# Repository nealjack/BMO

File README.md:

BMO
===

Code, Art and Design files to make BMO from adventure time

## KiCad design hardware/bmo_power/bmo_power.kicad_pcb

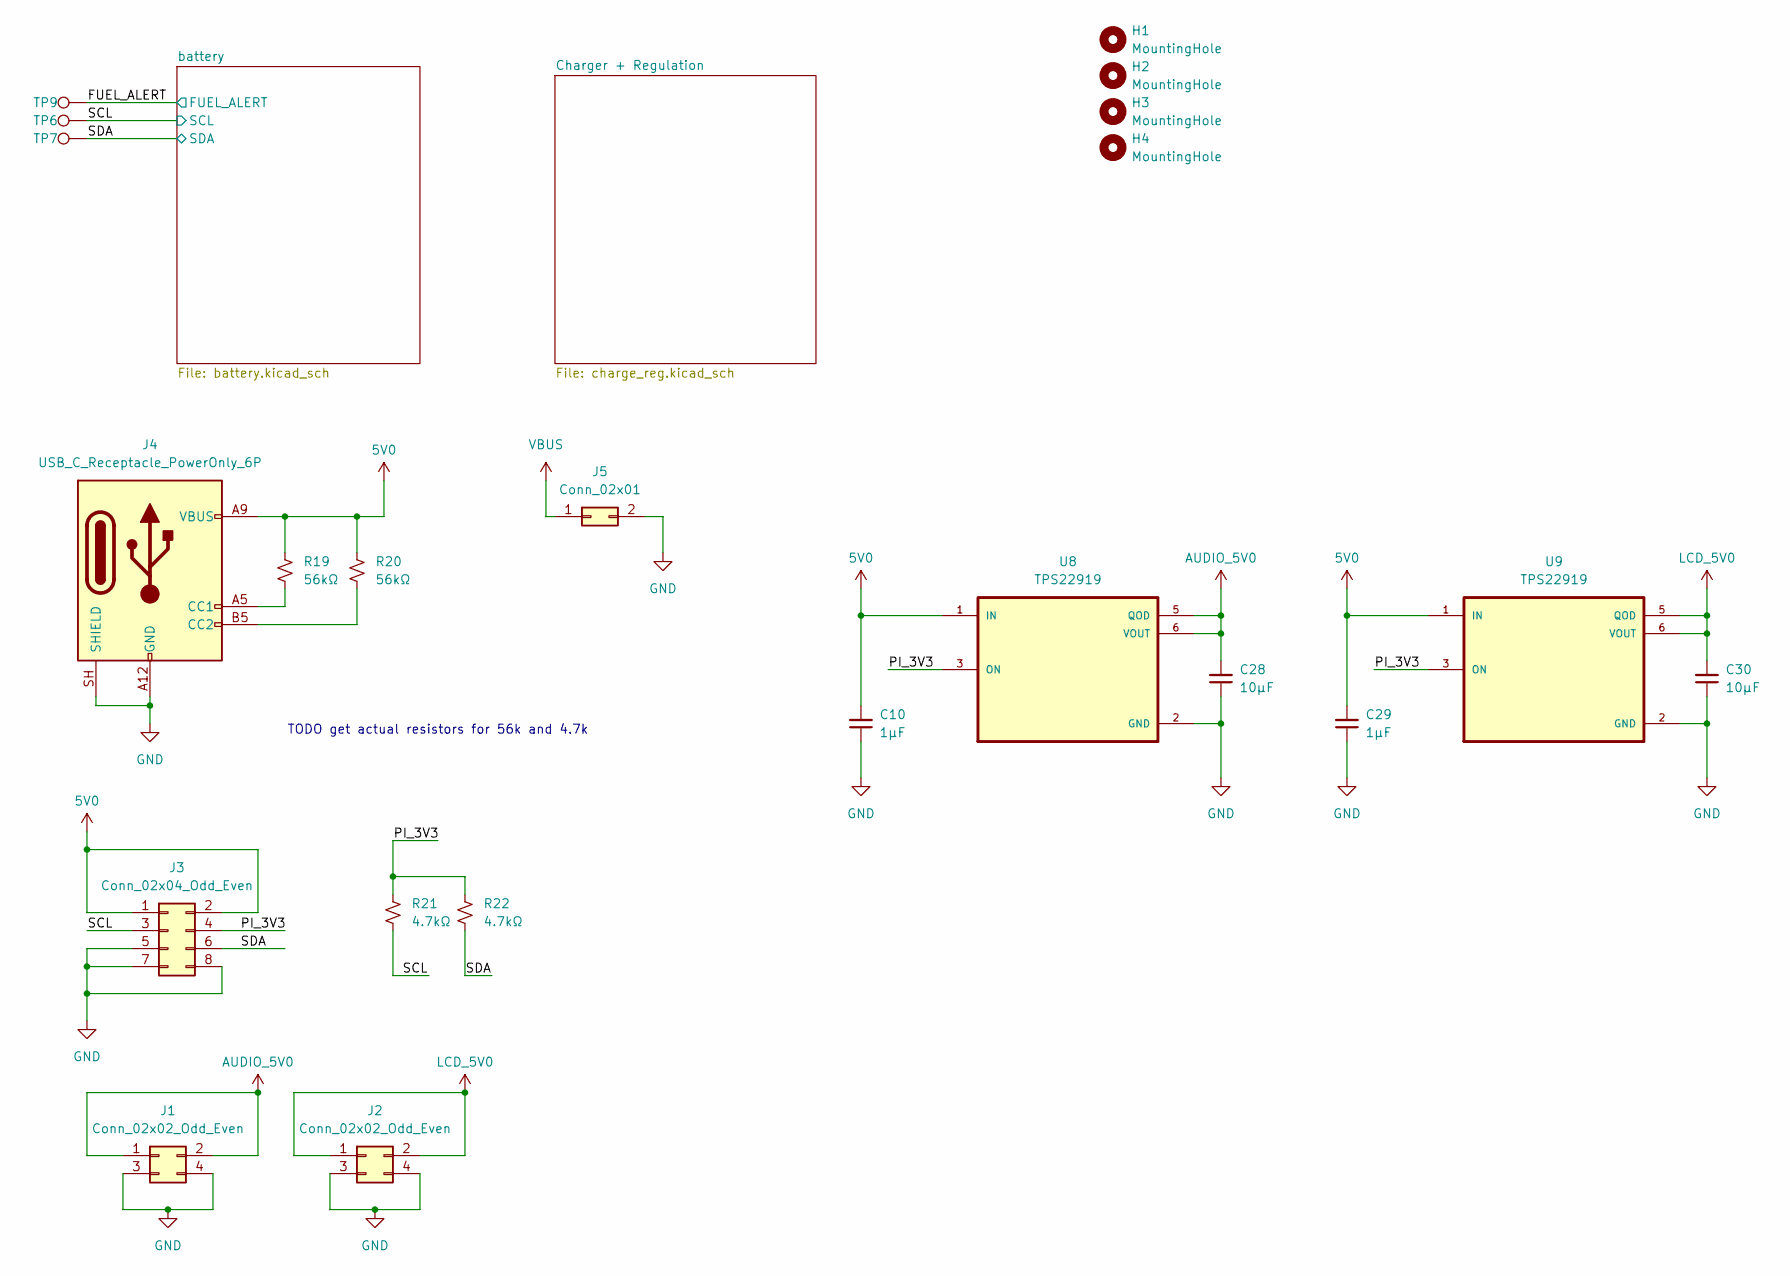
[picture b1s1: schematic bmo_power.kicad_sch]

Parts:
C10, C29: 1µF; C_0402_1005Metric_Pad0.74x0.62mm_HandSolder; MPN CL05A105KP5NNNC; Digikey 1276-1076-1-ND
C28, C30: 10µF; C_0402_1005Metric_Pad0.74x0.62mm_HandSolder; MPN GRM155R61A106ME11D; Digikey GRM155R61A106ME11D
H1, H2, H3, H4: MountingHole; MountingHole_2.7mm_M2.5
J1, J2: Conn_02x02_Odd_Even; PinHeader_2x02_P2.54mm_Vertical
J3: Conn_02x04_Odd_Even; PinHeader_2x04_P2.54mm_Vertical
J4: USB_C_Receptacle_PowerOnly_6P; USB_C_Receptacle_GCT_USB4125-xx-x-0190_6P_TopMnt_Horizontal
J5: Conn_02x01; PinSocket_2x01_P2.54mm_Vertical
R19, R20: 56kΩ; R_0402_1005Metric_Pad0.72x0.64mm_HandSolder; MPN RMCF0402FT10K0; Digikey RMCF0402FT10K0CT-ND
R21, R22: 4.7kΩ; R_0402_1005Metric_Pad0.72x0.64mm_HandSolder; MPN RMCF0402FT10K0; Digikey RMCF0402FT10K0CT-ND
TP6, TP7, TP9: TestPoint; TestPoint_Pad_2.0x2.0mm
U8, U9: TPS22919; SOT-363_SC-70-6

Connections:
5V0: C10.2, C29.2, J3.1, J3.2, J4.A9 (VBUS), J4.B9 (VBUS), R19.1, R20.1, U8.1 (IN), U9.1 (IN); also elsewhere on the board
/FUEL_ALERT: TP9.1 (1_1); also elsewhere on the board
/PI_3V3: J3.4, R21.1, R22.1, U8.3 (ON), U9.3 (ON)
/SCL: J3.3, R21.2, TP6.1 (1_1); also elsewhere on the board
/SDA: J3.6, R22.2, TP7.1 (1_1); also elsewhere on the board
AUDIO_5V0: C28.2, J1.1, J1.2, U8.5 (QOD), U8.6 (VOUT)
GND: C10.1, C28.1, C29.1, C30.1, J1.3, J1.4, J2.3, J2.4, J3.5, J3.7, J3.8, J4.A12 (GND), J4.B12 (GND), J4.SH (SHIELD), J5.2, U8.2 (GND), U9.2 (GND); also elsewhere on the board
LCD_5V0: C30.2, J2.1, J2.2, U9.5 (QOD), U9.6 (VOUT)
unnamed: J4.A5 (CC1), R19.2
unnamed: J4.B5 (CC2), R20.2
VBUS: J5.1; also elsewhere on the board

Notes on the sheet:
TODO get actual resistors for 56k and 4.7k

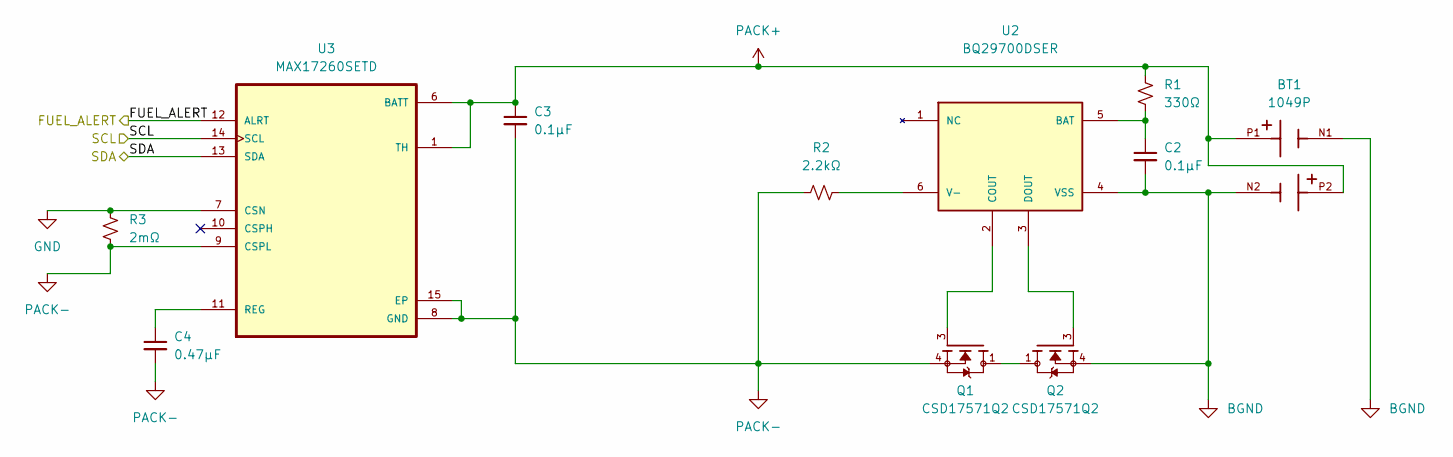
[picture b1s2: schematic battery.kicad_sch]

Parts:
BT1: 1049P; BAT_1049P; PARTREV F
C2, C3: 0.1μF; C_0402_1005Metric_Pad0.74x0.62mm_HandSolder; Tolerance 10%; Voltage 10V; MPN GRM155R61A104KA01D; Digikey 490-1318-2-ND
C4: 0.47μF; C_0402_1005Metric_Pad0.74x0.62mm_HandSolder; Tolerance 10%; Voltage 6.3V; MPN GRM155R60J474KE19D; Digikey 490-3266-1-ND
Q1, Q2: CSD17571Q2; TRANS_CSD17571Q2; PARTREV A
R1: 330Ω; R_0402_1005Metric_Pad0.72x0.64mm_HandSolder; MPN RMCF0402JT330R; Digikey RMCF0402JT330RCT-ND
R2: 2.2kΩ; R_0402_1005Metric_Pad0.72x0.64mm_HandSolder; Tolerance 5%; MPN RMCF0402JT2K20; Digikey RMCF0402JT2K20TR-ND
R3: 2mΩ; R_2512_6332Metric; Tolerance 1%; MPN CSNL2512FT2L00; Digikey CSNL2512FT2L00CT-ND
U2: BQ29700DSER; SON50P150X150X80-6N; PARTREV G
U3: MAX17260SETD; SON40P300X300X80-15N

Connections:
/FUEL_ALERT: U3.12 (ALRT); also elsewhere on the board
/SCL: U3.14 (SCL); also elsewhere on the board
/SDA: U3.13 (SDA); also elsewhere on the board
BGND: BT1.N1, BT1.N2, C2.2, Q2.4, Q2.8, U2.4 (VSS)
GND: R3.1, U3.7 (CSN); also elsewhere on the board
unnamed: Q1.1, Q1.2, Q1.5, Q1.6, Q1.7, Q2.1, Q2.2, Q2.5, Q2.6, Q2.7
unnamed: C2.1, R1.1, U2.5 (BAT)
unnamed: Q1.3, U2.2 (COUT)
unnamed: Q2.3, U2.3 (DOUT)
unnamed: R2.2, U2.6 (V-)
unnamed: C4.1, U3.11 (REG)
PACK+: BT1.P1, BT1.P2, C3.1, R1.2, U3.1 (TH), U3.6 (BATT); also elsewhere on the board
PACK-: C3.2, C4.2, Q1.4, Q1.8, R2.1, R3.2, U3.8 (GND), U3.9 (CSPL), U3.15 (EP)

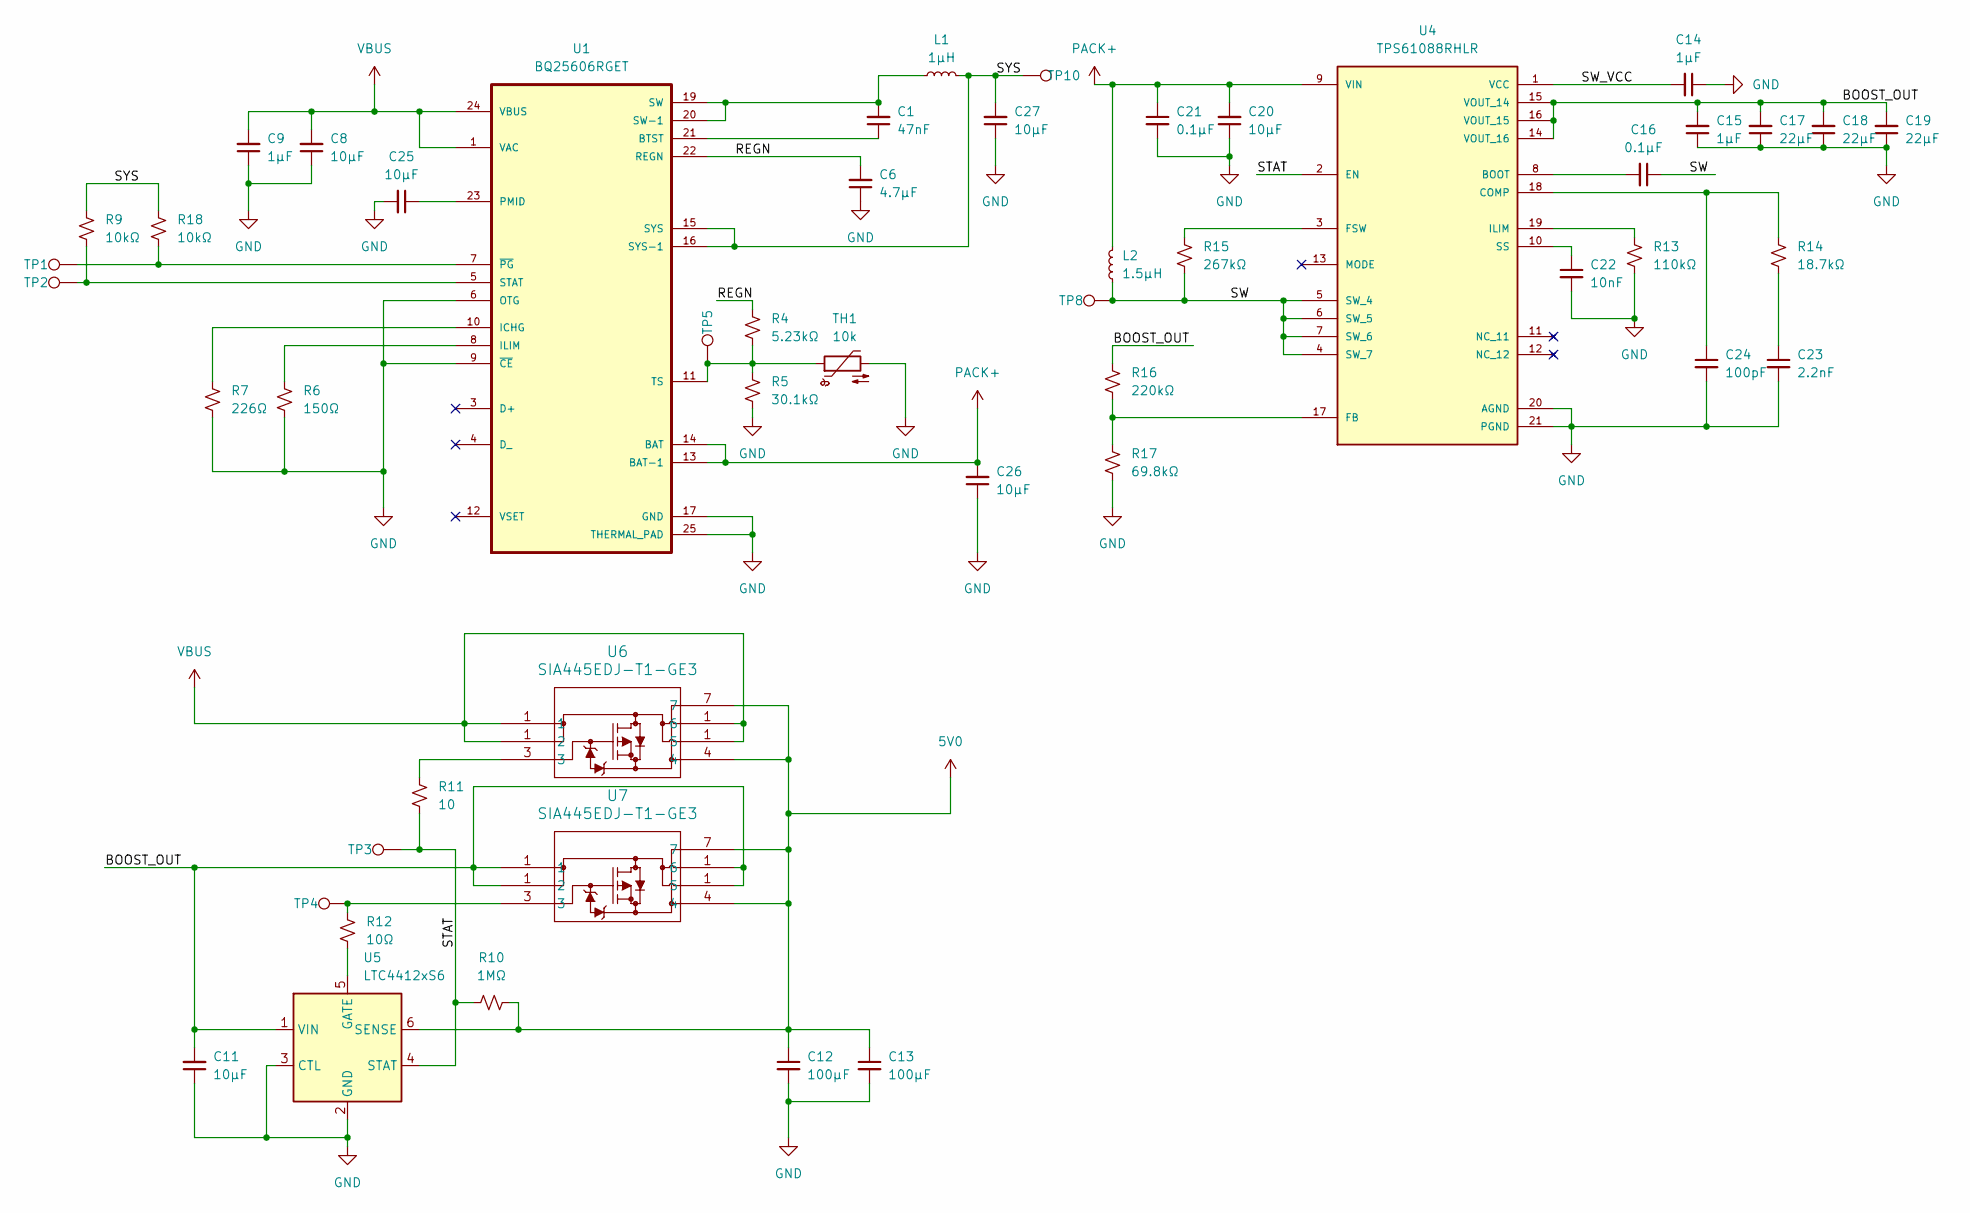
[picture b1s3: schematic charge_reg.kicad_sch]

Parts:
C1: 47nF; C_0402_1005Metric_Pad0.74x0.62mm_HandSolder; MPN GRM155R61A473KA01D; Digikey 490-5412-1-ND
C6: 4.7µF; C_0402_1005Metric_Pad0.74x0.62mm_HandSolder; MPN CL05A475MP5NRNC; Digikey 1276-1482-1-ND
C8, C11, C20, C25, C26, C27: 10µF; C_0402_1005Metric_Pad0.74x0.62mm_HandSolder; MPN GRM155R61A106ME11D; Digikey GRM155R61A106ME11D
C9, C14, C15: 1µF; C_0402_1005Metric_Pad0.74x0.62mm_HandSolder; MPN CL05A105KP5NNNC; Digikey 1276-1076-1-ND
C12, C13: 100µF; C_1206_3216Metric; MPN GRM31CR61A107MEA8L; Digikey 490-GRM31CR61A107MEA8LCT-ND
C16, C21: 0.1μF; C_0402_1005Metric_Pad0.74x0.62mm_HandSolder; Tolerance 10%; Voltage 10V; MPN GRM155R61A104KA01D; Digikey 490-1318-2-ND
C17, C18, C19: 22µF; C_0603_1608Metric; MPN CL10A226MP8NUNE; Digikey 1276-1274-1-ND
C22: 10nF; C_0402_1005Metric_Pad0.74x0.62mm_HandSolder; Tolerance 10%; Voltage 10V; MPN GRM155R61A103KA01D; Digikey 490-6296-1-ND
C23: 2.2nF; C_0402_1005Metric_Pad0.74x0.62mm_HandSolder; Tolerance 10%; Voltage 10V; MPN CC0402KRX7R6BB222; Digikey 311-3792-1-ND
C24: 100pF; C_0402_1005Metric_Pad0.74x0.62mm_HandSolder; Tolerance 10%; Voltage 10V; MPN CC0402KRX7R6BB101; Digikey 13-CC0402KRX7R6BB101CT-ND
L1: 1μH; L_Vishay_IHLP-2020; MPN IHLP2020ABER1R0M01; Digikey 541-1704-1-ND
L2: 1.5µH; 74439324015; MPN 74439324015; Digikey 732-74439324015CT-ND
R4: 5.23kΩ; R_0402_1005Metric_Pad0.72x0.64mm_HandSolder; MPN RC0402FR-075K23L; Digikey YAG3195CT-ND
R5: 30.1kΩ; R_0402_1005Metric_Pad0.72x0.64mm_HandSolder; MPN RC0402FR-0730K1L; Digikey 311-30.1KLRCT-ND
R6: 150Ω; R_0402_1005Metric_Pad0.72x0.64mm_HandSolder; MPN ERJ-2RKF1500X; Digikey P150LCT-ND
R7: 226Ω; R_0402_1005Metric_Pad0.72x0.64mm_HandSolder; MPN RMCF0402FT226R; Digikey RMCF0402FT226RCT-ND
R9, R18: 10kΩ; R_0402_1005Metric_Pad0.72x0.64mm_HandSolder; MPN RMCF0402FT10K0; Digikey RMCF0402FT10K0CT-ND
R10: 1MΩ; R_0402_1005Metric_Pad0.72x0.64mm_HandSolder; MPN RC0402FR-071ML; Digikey 311-1.00MLRCT-ND
R11: 10; R_0402_1005Metric_Pad0.72x0.64mm_HandSolder; MPN RC0402FR-0710RL; Digikey 311-10.0LRCT-ND
R12: 10Ω; R_0402_1005Metric_Pad0.72x0.64mm_HandSolder; MPN RC0402FR-0710RL; Digikey 311-10.0LRCT-ND
R13: 110kΩ; R_0402_1005Metric_Pad0.72x0.64mm_HandSolder; MPN RC0402FR-07110KL; Digikey 311-110KLRCT-ND
R14: 18.7kΩ; R_0402_1005Metric_Pad0.72x0.64mm_HandSolder; MPN RMCF0402FT18K7; Digikey RMCF0402FT18K7CT-ND
R15: 267kΩ; R_0402_1005Metric_Pad0.72x0.64mm_HandSolder; MPN RMCF0402FT267K; Digikey RMCF0402FT267KCT-ND
R16: 220kΩ; R_0402_1005Metric_Pad0.72x0.64mm_HandSolder; MPN RC0402FR-07220KL; Digikey 311-220KLRCT-ND
R17: 69.8kΩ; R_0402_1005Metric_Pad0.72x0.64mm_HandSolder; MPN RMCF0402FT69K8; Digikey RMCF0402FT69K8CT-ND
TH1: 10k; PinHeader_1x02_P2.54mm_Vertical; MPN 103AT-2; Digikey 4316-103AT-2-ND
TP1, TP2, TP3, TP4, TP5, TP8, TP10: TestPoint; TestPoint_Pad_2.0x2.0mm
U1: BQ25606RGET; QFN50P400X400X100-25N
U4: TPS61088RHLR; IC_TPS61088RHLR; PARTREV 4219071/A 05/2017
U5: LTC4412xS6; TSOT-23-6
U6, U7: SIA445EDJ-T1-GE3; Vishay_PowerPAK_SC70-6L_Single

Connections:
5V0: C12.1, C13.1, R10.2, U5.6 (SENSE), U6.4, U6.7, U7.4, U7.7; also elsewhere on the board
/Charger + Regulation/BOOST_OUT: C11.2, C15.2, C17.2, C18.2, C19.2, R16.1, U4.14 (VOUT_16), U4.15 (VOUT_14), U4.16 (VOUT_15), U5.1 (VIN), U7.1
/Charger + Regulation/REGN: C6.2, R4.1, U1.22 (REGN)
/Charger + Regulation/STAT: R10.1, R11.2, TP3.1 (1_1), U4.2 (EN), U5.4 (STAT)
/Charger + Regulation/SW: C16.1, L2.1, R15.2, TP8.1 (1_1), U4.4 (SW_7), U4.5 (SW_4), U4.6 (SW_5), U4.7 (SW_6)
/Charger + Regulation/SW_VCC: C14.2, U4.1 (VCC)
/Charger + Regulation/SYS: C27.2, L1.2, R9.1, R18.1, TP10.1 (1_1), U1.15 (SYS), U1.16 (SYS-1)
GND: C6.1, C8.1, C9.1, C11.1, C12.2, C13.2, C14.1, C15.1, C17.1, C18.1, C19.1, C20.1, C21.2, C22.2, C23.2, C24.2, C25.2, C26.1, C27.1, R5.2, R6.1, R7.1, R13.1, R17.2, TH1.2, U1.6 (OTG), U1.9 (~CE), U1.17 (GND), U1.18 (GND), U1.25 (THERMAL_PAD), U4.20 (AGND), U4.21 (PGND), U4.22 (PGND), U4.23 (PGND), U4.24 (PGND), U4.25 (PGND), U4.26 (PGND), U4.27 (PGND), U4.28 (PGND), U4.29 (PGND), U5.2 (GND), U5.3 (CTL); also elsewhere on the board
unnamed: C23.1, R14.1
unnamed: R11.1, U6.3
unnamed: R12.1, TP4.1 (1_1), U7.3
unnamed: C1.1, U1.21 (BTST)
unnamed: R7.2, U1.10 (ICHG)
unnamed: R6.2, U1.8 (ILIM)
unnamed: C25.1, U1.23 (PMID)
unnamed: R9.2, TP2.1 (1_1), U1.5 (STAT)
unnamed: C1.2, L1.1, U1.19 (SW), U1.20 (SW-1)
unnamed: R4.2, R5.1, TH1.1, TP5.1 (1_1), U1.11 (TS)
unnamed: R18.2, TP1.1 (1_1), U1.7 (~PG)
unnamed: C16.2, U4.8 (BOOT)
unnamed: C24.1, R14.2, U4.18 (COMP)
unnamed: R16.2, R17.1, U4.17 (FB)
unnamed: R15.1, U4.3 (FSW)
unnamed: R13.2, U4.19 (ILIM)
unnamed: C22.1, U4.10 (SS)
unnamed: R12.2, U5.5 (GATE)
PACK+: C20.2, C21.1, C26.2, L2.2, U1.13 (BAT-1), U1.14 (BAT), U4.9 (VIN); also elsewhere on the board
VBUS: C8.2, C9.2, U1.1 (VAC), U1.24 (VBUS), U6.1; also elsewhere on the board

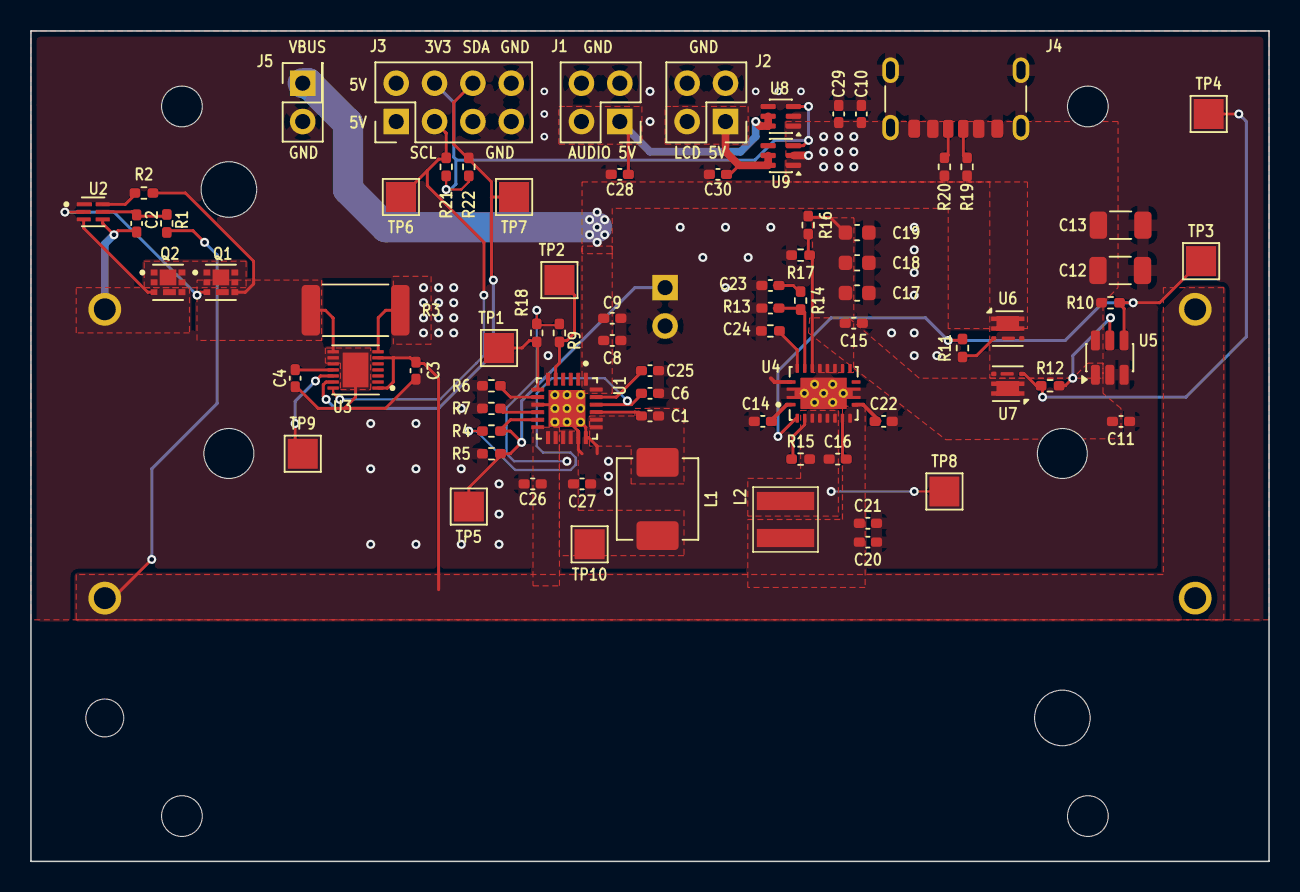
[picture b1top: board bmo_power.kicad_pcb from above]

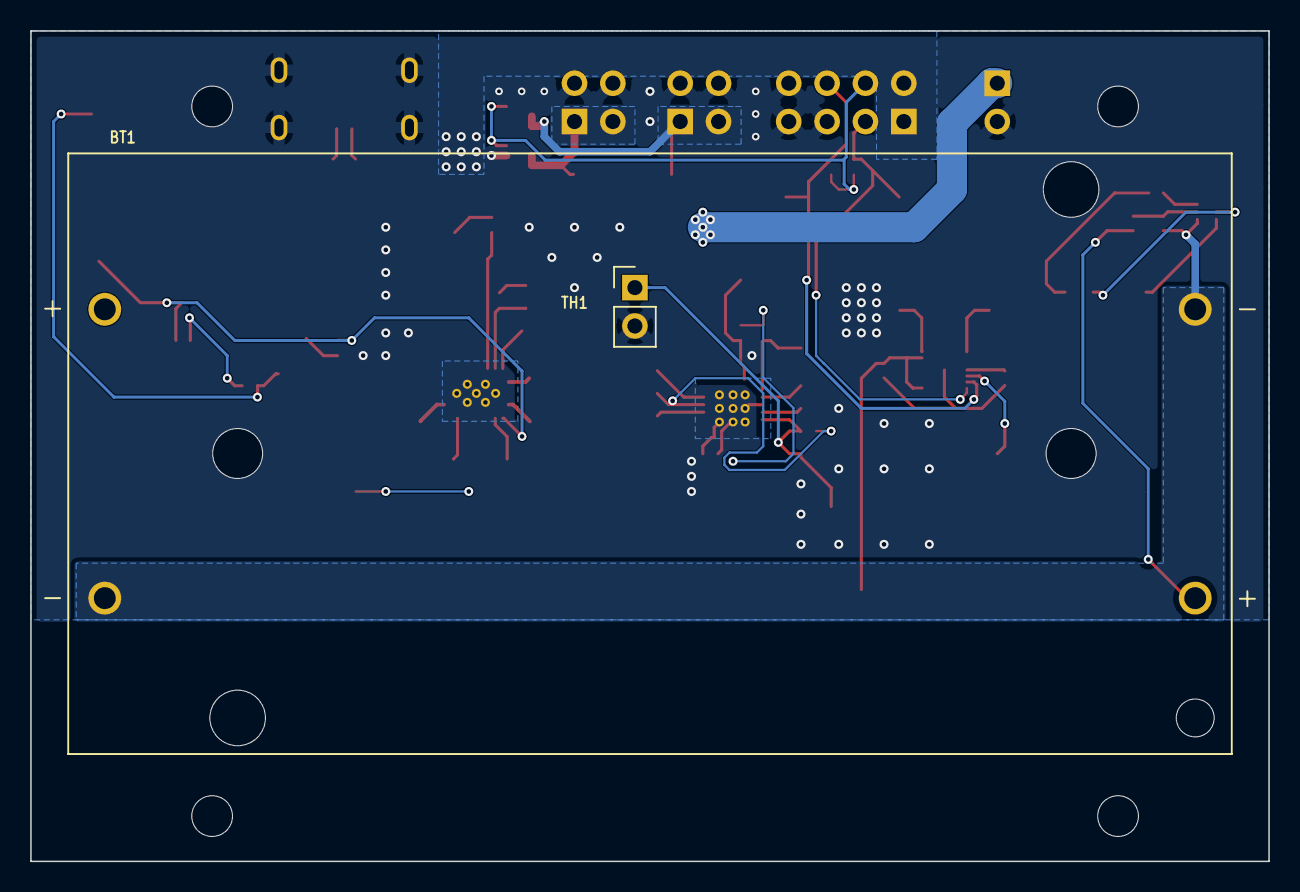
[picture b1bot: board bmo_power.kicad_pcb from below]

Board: 2 copper layers, 82.0 x 55.0 mm, 83 parts (2 on the bottom side), 44 nets.

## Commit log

2014-07-27 initial push
2014-07-27 cleaned up body dir
2016-04-28 reorganization
2016-04-28 schematic for button pcb
2016-06-26 Start of button PCB Need to fit teensy on same board, reduce the amount of mapped out pins
2016-07-01 First stab at button board Fits current body model, faceplate needs spacing of start/select
2016-07-01 Designs largely finished for body and front
2016-07-01 Back and panel not quite done or tested, but should fit
2016-07-02 Start USB board, add some usb hub parts to lbr
2016-07-02 Tweak back panel; add other unfinished designs
2016-07-03 finished usb schematic
2016-07-04 start of board, might need to restart
2016-07-04 usb board done
2016-07-04 tweaking size, added power header
2016-07-05 cleanup
2016-07-05 Fitted board to case, added silkscreen
2016-07-05 fix one last cap
2016-07-06 Tweaks to body and integration of chip holder
2016-07-07 Added boards for back buttons and charging/serial port Tweaks and redesigns for button/usb boards to fit in case better
2016-07-07 Shipped to OSHPark added merge.cfg for use with gerbmerge
2016-07-08 added bom, need to combine
2016-07-08 Added BOM Next rev needs to change pad sizes for 0603 and larger parts I forgot to take into account the sizing of inductors and caps with larger values. C9,C10,C11 are set to 47uF for this rev, shou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
2017-05-11 random changes not committed from this summer
2017-05-27 add full teensy layout
2017-05-27 start revb
2026-05-03 Add wip power board
2026-05-03 wip start ltc4412 addition
2026-06-13 Placed and routed everything. DRC is clean.
2026-06-13 rename to bmo_power for power board
2026-06-14 embed 3d models
2026-06-14 first try adding kibot
2026-06-14 add workflow dispatch option
2026-06-14 fix paths
